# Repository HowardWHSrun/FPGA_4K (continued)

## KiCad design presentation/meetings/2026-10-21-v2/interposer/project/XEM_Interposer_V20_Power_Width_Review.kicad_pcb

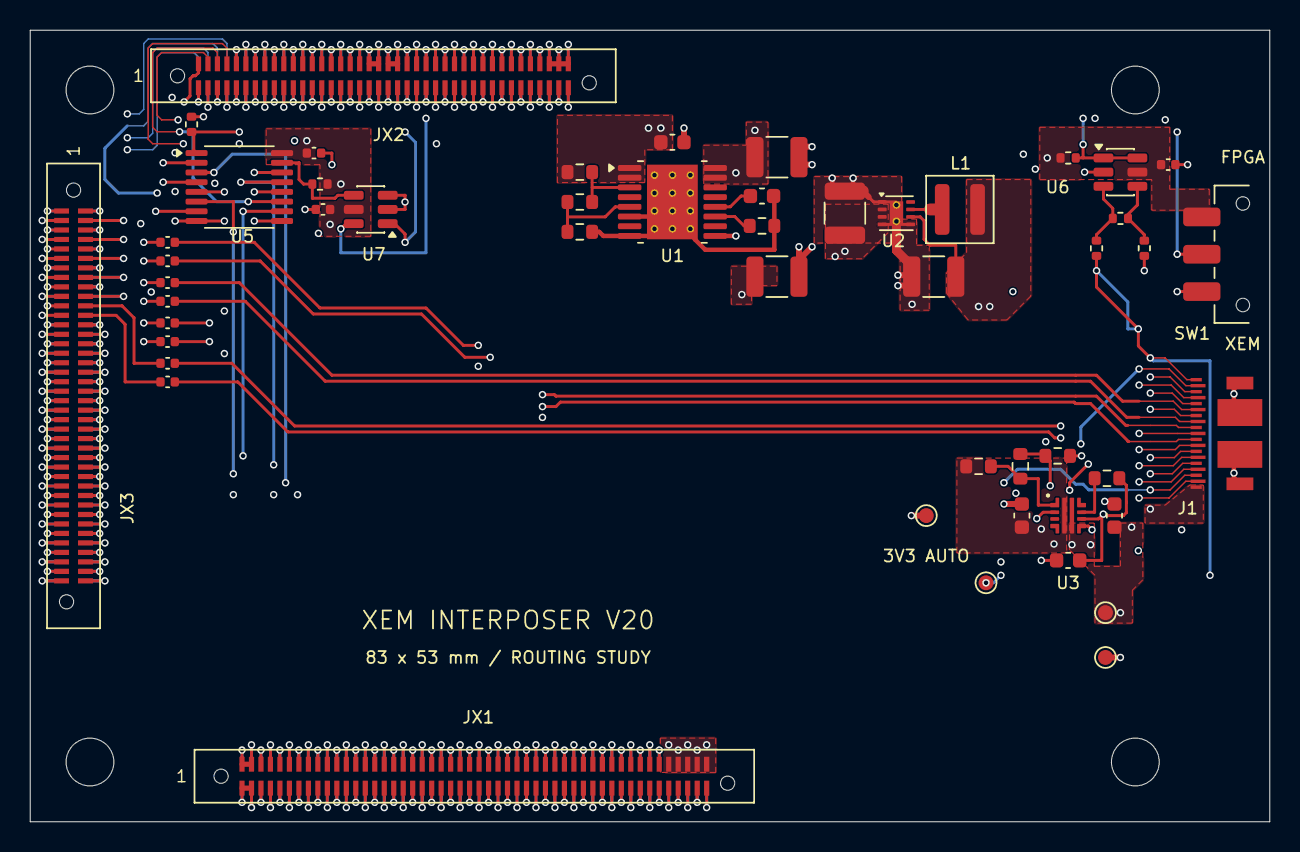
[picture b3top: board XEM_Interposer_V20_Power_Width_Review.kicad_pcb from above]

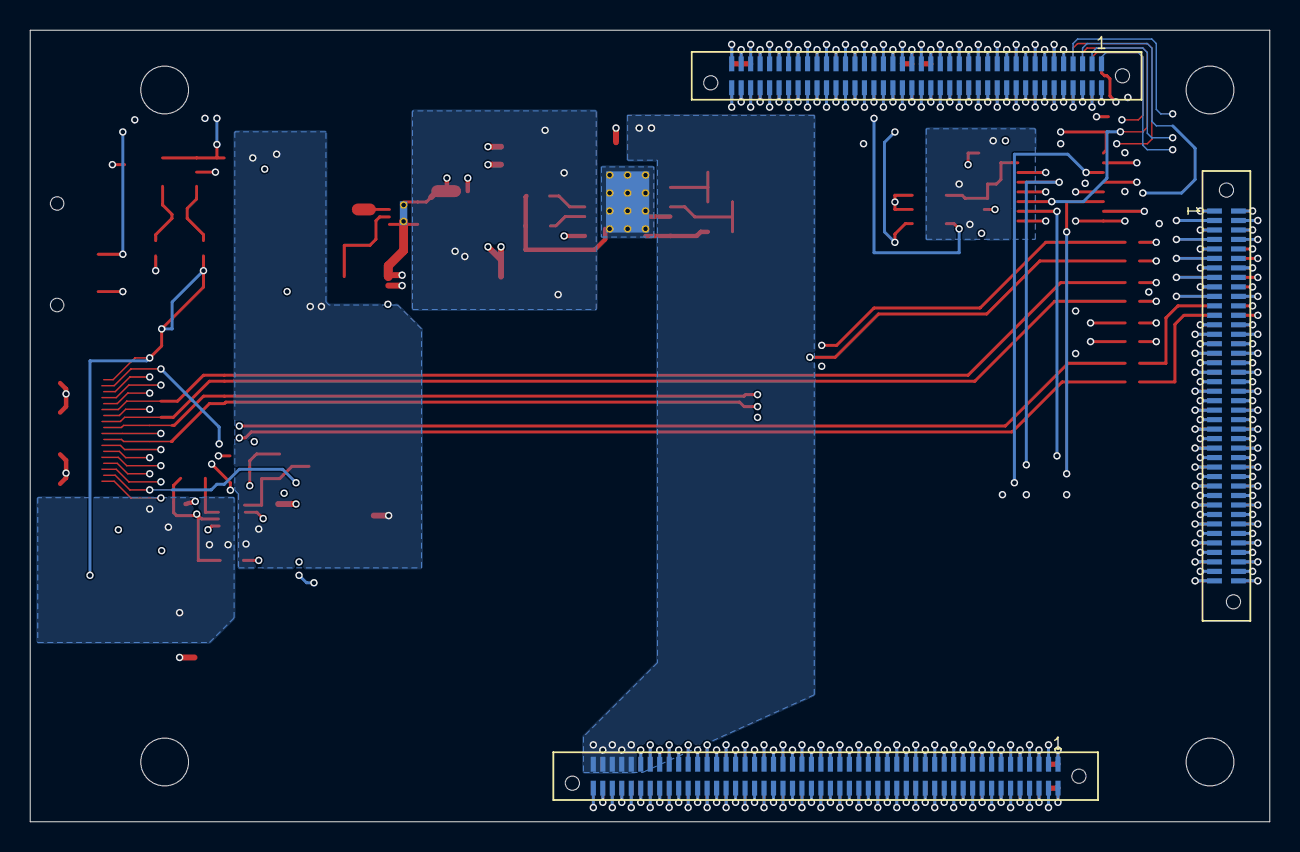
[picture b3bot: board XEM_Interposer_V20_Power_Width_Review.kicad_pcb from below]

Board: 6 copper layers, 83.0 x 53.0 mm, 57 parts (3 on the bottom side), 234 nets.

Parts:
C1: 1 µF / 50 V; C_0603_1608Metric
C2: 22 nF / 50 V; C_0603_1608Metric
C3, C10, C11: 10 uF / 50 V; C_1210_3225Metric
C4: 22 µF / 25 V; C_1210_3225Metric
C5, C7: 1 µF / 10 V; C_0603_1608Metric
C6: 3.3 nF / 10 V; C_0603_1608Metric
C12, C13, C14, C15, C16, C17, C18, C19: 100 nF / 16 V; C_0402_1005Metric
C20, C21, C22: 100 nF / 10 V; C_0402_1005Metric
J1: PKS019-4011-0; PKS019-4011-0_A114106_001_RevA_V17
JB1: ERM6-50-01.5-L-DV-A-K-TR; ERM6-50-01.5-L-DV-A-K-TR_SharedHoles_V16
JB2, JB3: ERM6-40-01.5-L-DV-A-K-TR; ERM6-40-01.5-L-DV-A-K-TR_SharedHoles_V16
JX1: ERF6-50-03.5-L-DV-A-K-TR
JX2, JX3: ERF6-40-03.5-L-DV-A-K-TR
L1: 2.2 µH; L_Coilcraft_XAL4020-XXX
MH1, MH2, MH3, MH4: 3.2 mm mounting datum
R1: 1.05 MΩ; R_0603_1608Metric
R2: 78.7 kΩ; R_0603_1608Metric
R3, R7: 100 kΩ; R_0603_1608Metric
R4: 12.1 kΩ; R_0603_1608Metric
R5: 174 kΩ; R_0603_1608Metric
R6: 24.9 kΩ; R_0603_1608Metric
R8: 6.49 kΩ; R_0603_1608Metric
R11: 75.0 k / 0.1%; R_0402_1005Metric
R12: 3.83 k / 0.1%; R_0402_1005Metric
R13: 20.0 k / 0.1%; R_0402_1005Metric
R14: 10 k; R_0402_1005Metric
R15: 47.0 k / 1%; R_0402_1005Metric
R16: 100 k; R_0402_1005Metric
SW1: JS102011SABN; SW_SPDT_CK_JS102011SABN
TP1: 3V3 LOCAL; TestPoint_Pad_D1.0mm
TP2: 3V3 CABLE; TestPoint_Pad_D1.0mm
TP3: TARGET 1V8 SENSE; TestPoint_Pad_D1.0mm
TP4: GND; TestPoint_Pad_D1.0mm
U1: TPS26600PWPR; HTSSOP-16-1EP_4.4x5mm_P0.65mm_EP3.4x5mm_Mask2.66x2.46mm_The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
U2: TPS62162DSGR; Texas_DSG0008A_WSON-8-1EP_2x2mm_P0.5mm_EP0.9x1.6mm_ThermalV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
U3: TPS259470ARPWR; TI_RPW0010A_HotRod_2x2mm
U5: TMUX1574PWR; TSSOP-16_4.4x5mm_P0.65mm
U6: TLV6700DDCR; SOT-23-6
U7: SN74LVC1G97DBVR; SOT-23-6

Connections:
+3V3_CABLE: C7.1, J1.19 (3V3_OUT), TP2.1 (1_1), U3.6 (OUT)
+3V3_LOCAL: C4.1, C5.1, C20.1, C21.1, C22.1, L1.2, R5.1, R14.1, R16.1, SW1.3, TP1.1 (1_1), U2.6 (VOS), U3.5 (IN), U5.16 (VDD), U6.5 (VDD), U7.5 (VCC)
/JTAG_DISABLE: R16.2, U5.15 (~EN), U7.4 (Y)
/JTAG_REMOTE_SELECT: R15.1, SW1.2 (C), U5.1 (SEL), U7.1 (IN1)
/TARGET_1V8_SENSE: J1.1 (TARGET_SENSE), R11.1, TP3.1 (1_1)
/TARGET_GOOD: R14.2, U6.1 (OUTA), U6.6 (OUTB), U7.6 (IN2)
/TARGET_OV_TAP: R12.2, R13.1, U6.4 (INB-)
/TARGET_TCK: J1.17 (TCK_1V8), U5.3 (S1B)
/TARGET_TDI: J1.15 (TDI_1V8), U5.6 (S2B)
/TARGET_TDO: J1.18 (TDO_1V8), U5.13 (S4B)
/TARGET_TMS: J1.2 (TMS_1V8), U5.10 (S3B)
/TARGET_UV_TAP: R11.2, R12.1, U6.3 (INA+)
BRK_REFCLK226_N: JB2.4 (REFCLK0N_226), JX2.4 (REFCLK0N_226)
BRK_REFCLK226_P: JB2.2 (REFCLK0P_226), JX2.2 (REFCLK0P_226)
BRK_TCK: JB2.1 (JTAG_TCK), U5.4 (D1)
BRK_TDI: JB2.3 (JTAG_TDI), U5.7 (D2)
BRK_TDO: JB2.7 (JTAG_TDO), U5.12 (D4)
BRK_TMS: JB2.5 (JTAG_TMS), U5.9 (D3)
BRK_VDCIN: C1.1, JB1.91 (VDCIN), JB1.93 (VDCIN), JB1.95 (VDCIN), JB1.97 (VDCIN), JB1.99 (VDCIN), JX1.91 (VDCIN), JX1.93 (VDCIN), JX1.95 (VDCIN), JX1.97 (VDCIN), JX1.99 (VDCIN), R1.1, U1.1 (IN), U1.2 (IN)
FPGA_RX1_N: C19.1, J1.14 (FPGA_RX1_N)
FPGA_RX1_P: C18.1, J1.12 (FPGA_RX1_P)
FPGA_TX0_N: C13.1, J1.5 (FPGA_TX0_N)
FPGA_TX0_P: C12.1, J1.3 (FPGA_TX0_P)
FPGA_TX1_N: C15.1, J1.8 (FPGA_TX1_N)
FPGA_TX1_P: C14.1, J1.6 (FPGA_TX1_P)
FPGA_TX2_N: C17.1, J1.11 (FPGA_TX2_N)
FPGA_TX2_P: C16.1, J1.9 (FPGA_TX2_P)
GND: C1.2, C3.2, C4.2, C5.2, C6.2, C7.2, C10.2, C11.2, C20.2, C21.2, C22.2, J1.4 (GND), J1.7 (GND), J1.10 (GND), J1.13 (GND), J1.16 (GND), J1.SH (SHELL), JB1.5 (GND), JB1.6 (GND), JB1.7 (GND), JB1.8 (GND), JB1.33 (GND), JB1.34 (GND), JB1.61 (GND), JB1.62 (GND), JB1.92 (GND), JB1.94 (GND), JB1.96 (GND), JB1.98 (GND), JB1.100 (GND), JB2.6 (GND), JB2.9 (GND), JB2.20 (GND), JB2.35 (GND), JB2.45 (GND), JB2.46 (GND), JB2.47 (GND), JB2.72 (GND), JB2.73 (GND), JB2.74 (GND), JB2.76 (GND), JB3.1 (GND), JB3.2 (GND), JB3.7 (GND), JB3.8 (GND), JB3.13 (GND), JB3.14 (GND), JB3.19 (GND), JB3.20 (GND), JB3.25 (GND), JB3.26 (GND), JB3.31 (GND), JB3.32 (GND), JB3.37 (GND), JB3.38 (GND), JB3.43 (GND), JB3.44 (GND), JB3.49 (GND), JB3.50 (GND), JB3.55 (GND), JB3.56 (GND), JB3.61 (GND), JB3.62 (GND), JB3.67 (GND), JB3.68 (GND), JB3.73 (GND), JB3.74 (GND), JB3.79 (GND), JB3.80 (GND), JX1.5 (GND), JX1.6 (GND), JX1.7 (GND), JX1.8 (GND), JX1.33 (GND), JX1.34 (GND), JX1.61 (GND), JX1.62 (GND), JX1.92 (GND), JX1.94 (GND), JX1.96 (GND), JX1.98 (GND), JX1.100 (GND), JX2.6 (GND), JX2.9 (GND), JX2.20 (GND), JX2.35 (GND), JX2.45 (GND), JX2.46 (GND), JX2.47 (GND), JX2.72 (GND), JX2.73 (GND), JX2.74 (GND), JX2.76 (GND), JX3.1 (GND), JX3.2 (GND), JX3.7 (GND), JX3.8 (GND), JX3.13 (GND), JX3.14 (GND), JX3.19 (GND), JX3.20 (GND), JX3.25 (GND), JX3.26 (GND), JX3.31 (GND), JX3.32 (GND), JX3.37 (GND), JX3.38 (GND), JX3.43 (GND), JX3.44 (GND), JX3.49 (GND), JX3.50 (GND), JX3.55 (GND), JX3.56 (GND), JX3.61 (GND), JX3.62 (GND), JX3.67 (GND), JX3.68 (GND), JX3.73 (GND), JX3.74 (GND), JX3.79 (GND), JX3.80 (GND), R7.2, R8.2, R13.2, R15.2, SW1.1, TP4.1 (1_1), U1.9 (GND), U2.1 (PGND), U2.4 (AGND), U2.5 (FB), U2.9 (EP), U3.8 (GND), U5.8 (GND), U6.2 (GND), U7.2 (GND), U7.3 (IN0)
INPUT_RTN: C2.2, R3.2, R4.2, U1.6 (MODE), U1.8 (RTN), U1.17 (RTN)
unnamed: C13.2, JX3.24 (MGT_RXN0_226)
unnamed: C15.2, JX3.18 (MGT_RXN1_226)
unnamed: C17.2, JX3.12 (MGT_RXN2_226)
unnamed: C12.2, JX3.22 (MGT_RXP0_226)
unnamed: C14.2, JX3.16 (MGT_RXP1_226)
unnamed: C16.2, JX3.10 (MGT_RXP2_226)
unnamed: C19.2, JX3.23 (MGT_TXN0_226)
unnamed: C18.2, JX3.21 (MGT_TXP0_226)
unnamed: R4.1, U1.11 (ILIM)
unnamed: R2.2, R3.1, U1.5 (OVP)
unnamed: R1.2, R2.1, U1.3 (UVLO)
unnamed: C2.1, U1.12 (dVdT)
unnamed: L1.1, U2.7 (SW)
unnamed: R5.2, R6.1, U3.1 (EN/UVLO)
unnamed: R8.1, U3.9 (ILM)
unnamed: R6.2, R7.1, U3.2 (OVLO)
unnamed: C6.1, U3.7 (dVdt)
PROTECTED_12V: C3.1, C10.1, C11.1, U1.15 (OUT), U1.16 (OUT), U2.2 (VIN), U2.3 (EN)
STACK_MC1_09: JB1.9 (B84_L7P_HDGC), JX1.9 (B84_L7P_HDGC)
STACK_MC1_10: JB1.10 (B84_L1P), JX1.10 (B84_L1P)
STACK_MC1_11: JB1.11 (B84_L7N_HDGC), JX1.11 (B84_L7N_HDGC)
STACK_MC1_12: JB1.12 (B84_L1N), JX1.12 (B84_L1N)
STACK_MC1_13: JB1.13 (B84_L8P_HDGC), JX1.13 (B84_L8P_HDGC)
STACK_MC1_14: JB1.14 (B84_L2P), JX1.14 (B84_L2P)
STACK_MC1_15: JB1.15 (B84_L8N_HDGC), JX1.15 (B84_L8N_HDGC)
STACK_MC1_16: JB1.16 (B84_L2N), JX1.16 (B84_L2N)
STACK_MC1_17: JB1.17 (B84_L9P), JX1.17 (B84_L9P)
STACK_MC1_18: JB1.18 (B84_L3P), JX1.18 (B84_L3P)
STACK_MC1_19: JB1.19 (B84_L9N), JX1.19 (B84_L9N)
STACK_MC1_20: JB1.20 (B84_L3N), JX1.20 (B84_L3N)
STACK_MC1_21: JB1.21 (B84_L10P), JX1.21 (B84_L10P)
STACK_MC1_22: JB1.22 (B84_L4P), JX1.22 (B84_L4P)
STACK_MC1_23: JB1.23 (B84_L10N), JX1.23 (B84_L10N)
STACK_MC1_24: JB1.24 (B84_L4N), JX1.24 (B84_L4N)
STACK_MC1_25: JB1.25 (B84_L11P), JX1.25 (B84_L11P)
STACK_MC1_26: JB1.26 (B84_L5P_HDGC), JX1.26 (B84_L5P_HDGC)
STACK_MC1_27: JB1.27 (B84_L11N), JX1.27 (B84_L11N)
STACK_MC1_28: JB1.28 (B84_L5N_HDGC), JX1.28 (B84_L5N_HDGC)
STACK_MC1_29: JB1.29 (B84_L12P), JX1.29 (B84_L12P)
STACK_MC1_30: JB1.30 (B84_L6P_HDGC), JX1.30 (B84_L6P_HDGC)
STACK_MC1_31: JB1.31 (B84_L12N), JX1.31 (B84_L12N)
STACK_MC1_32: JB1.32 (B84_L6N_HDGC), JX1.32 (B84_L6N_HDGC)
STACK_MC1_35: JB1.35 (B64_L24P), JX1.35 (B64_L24P)
STACK_MC1_36: JB1.36 (B64_L18P), JX1.36 (B64_L18P)
STACK_MC1_37: JB1.37 (B64_L24N), JX1.37 (B64_L24N)
STACK_MC1_38: JB1.38 (B64_L18N), JX1.38 (B64_L18N)
STACK_MC1_39: JB1.39 (B64_L23P), JX1.39 (B64_L23P)
STACK_MC1_40: JB1.40 (B64_L17P), JX1.40 (B64_L17P)
STACK_MC1_41: JB1.41 (B64_L23N), JX1.41 (B64_L23N)
STACK_MC1_42: JB1.42 (B64_L17N), JX1.42 (B64_L17N)
STACK_MC1_43: JB1.43 (B64_L22P), JX1.43 (B64_L22P)
STACK_MC1_44: JB1.44 (B64_L16P), JX1.44 (B64_L16P)
STACK_MC1_45: JB1.45 (B64_L22N), JX1.45 (B64_L22N)
STACK_MC1_46: JB1.46 (B64_L16N), JX1.46 (B64_L16N)
STACK_MC1_47: JB1.47 (B64_L21P), JX1.47 (B64_L21P)
STACK_MC1_48: JB1.48 (B64_L15P), JX1.48 (B64_L15P)
STACK_MC1_49: JB1.49 (B64_L21N), JX1.49 (B64_L21N)
STACK_MC1_50: JB1.50 (B64_L15N), JX1.50 (B64_L15N)
STACK_MC1_51: JB1.51 (B64_L20P), JX1.51 (B64_L20P)
STACK_MC1_52: JB1.52 (B64_L14P_GC), JX1.52 (B64_L14P_GC)
STACK_MC1_53: JB1.53 (B64_L20N), JX1.53 (B64_L20N)
STACK_MC1_54: JB1.54 (B64_L14N_GC), JX1.54 (B64_L14N_GC)
STACK_MC1_55: JB1.55 (B64_L19P), JX1.55 (B64_L19P)
STACK_MC1_56: JB1.56 (B64_L13P_GC), JX1.56 (B64_L13P_GC)
STACK_MC1_57: JB1.57 (B64_L19N), JX1.57 (B64_L19N)
STACK_MC1_58: JB1.58 (B64_L13N_GC), JX1.58 (B64_L13N_GC)
STACK_MC1_59: JB1.59 (B64_T3U_N12), JX1.59 (B64_T3U_N12)
STACK_MC1_60: JB1.60 (B64_T2U_N12), JX1.60 (B64_T2U_N12)
STACK_MC1_63: JB1.63 (B64_L12P_GC), JX1.63 (B64_L12P_GC)
STACK_MC1_64: JB1.64 (B64_L6P), JX1.64 (B64_L6P)
STACK_MC1_65: JB1.65 (B64_L12N_GC), JX1.65 (B64_L12N_GC)
STACK_MC1_66: JB1.66 (B64_L6N), JX1.66 (B64_L6N)
STACK_MC1_67: JB1.67 (B64_L11P_GC), JX1.67 (B64_L11P_GC)
STACK_MC1_68: JB1.68 (B64_L5P), JX1.68 (B64_L5P)
STACK_MC1_69: JB1.69 (B64_L11N_GC), JX1.69 (B64_L11N_GC)
STACK_MC1_70: JB1.70 (B64_L5N), JX1.70 (B64_L5N)
STACK_MC1_71: JB1.71 (B64_L10P), JX1.71 (B64_L10P)
STACK_MC1_72: JB1.72 (B64_L4P), JX1.72 (B64_L4P)
STACK_MC1_73: JB1.73 (B64_L10N), JX1.73 (B64_L10N)
STACK_MC1_74: JB1.74 (B64_L4N), JX1.74 (B64_L4N)
STACK_MC1_75: JB1.75 (B64_L9P), JX1.75 (B64_L9P)
STACK_MC1_76: JB1.76 (B64_L3P), JX1.76 (B64_L3P)
STACK_MC1_77: JB1.77 (B64_L9N), JX1.77 (B64_L9N)
STACK_MC1_78: JB1.78 (B64_L3N), JX1.78 (B64_L3N)
STACK_MC1_79: JB1.79 (B64_L8P), JX1.79 (B64_L8P)
STACK_MC1_80: JB1.80 (B64_L2P), JX1.80 (B64_L2P)
STACK_MC1_81: JB1.81 (B64_L8N), JX1.81 (B64_L8N)
STACK_MC1_82: JB1.82 (B64_L2N), JX1.82 (B64_L2N)
STACK_MC1_83: JB1.83 (B64_L7P), JX1.83 (B64_L7P)
STACK_MC1_84: JB1.84 (B64_L1P), JX1.84 (B64_L1P)
STACK_MC1_85: JB1.85 (B64_L7N), JX1.85 (B64_L7N)
STACK_MC1_86: JB1.86 (B64_L1N), JX1.86 (B64_L1N)
STACK_MC1_87: JB1.87 (RESERVED1), JX1.87 (RESERVED1)
STACK_MC1_88: JB1.88 (B64_T1U_N12), JX1.88 (B64_T1U_N12)
STACK_MC1_89: JB1.89 (VREF_64), JX1.89 (VREF_64)
STACK_MC1_90: JB1.90 (XEM8305_PG), JX1.90 (XEM8305_PG)
STACK_MC2_08: JB2.8 (VBATT), JX2.8 (VBATT)
STACK_MC2_10: JB2.10 (XADC_VN), JX2.10 (XADC_VN)
STACK_MC2_11: JB2.11 (B85_L1P), JX2.11 (B85_L1P)
STACK_MC2_12: JB2.12 (XADC_VP), JX2.12 (XADC_VP)
STACK_MC2_13: JB2.13 (B85_L1N), JX2.13 (B85_L1N)
STACK_MC2_14: JB2.14 (VREFP), JX2.14 (VREFP)
STACK_MC2_15: JB2.15 (B85_L2P), JX2.15 (B85_L2P)
STACK_MC2_16: JB2.16 (GNDADC), JX2.16 (GNDADC)
STACK_MC2_17: JB2.17 (B85_L2N), JX2.17 (B85_L2N)
STACK_MC2_18: JB2.18 (VCCADC), JX2.18 (VCCADC)
STACK_MC2_19: JB2.19 (B85_L3P), JX2.19 (B85_L3P)
STACK_MC2_21: JB2.21 (B85_L3N), JX2.21 (B85_L3N)
STACK_MC2_22: JB2.22 (B85_L7P_HDGC), JX2.22 (B85_L7P_HDGC)
STACK_MC2_23: JB2.23 (B85_L4P), JX2.23 (B85_L4P)
STACK_MC2_24: JB2.24 (B85_L7N_HDGC), JX2.24 (B85_L7N_HDGC)
STACK_MC2_25: JB2.25 (B85_L4N), JX2.25 (B85_L4N)
STACK_MC2_26: JB2.26 (B85_L8P_HDGC), JX2.26 (B85_L8P_HDGC)
STACK_MC2_27: JB2.27 (B85_L5P_HDGC), JX2.27 (B85_L5P_HDGC)
STACK_MC2_28: JB2.28 (B85_L8N_HDGC), JX2.28 (B85_L8N_HDGC)
STACK_MC2_29: JB2.29 (B85_L5N_HDGC), JX2.29 (B85_L5N_HDGC)
STACK_MC2_30: JB2.30 (B85_L9P), JX2.30 (B85_L9P)
STACK_MC2_31: JB2.31 (B85_L6P_HDGC), JX2.31 (B85_L6P_HDGC)
STACK_MC2_32: JB2.32 (B85_L9N), JX2.32 (B85_L9N)
STACK_MC2_33: JB2.33 (B85_L6N_HDGC), JX2.33 (B85_L6N_HDGC)
STACK_MC2_34: JB2.34 (B85_L10P), JX2.34 (B85_L10P)
STACK_MC2_36: JB2.36 (B85_L10N), JX2.36 (B85_L10N)
STACK_MC2_38: JB2.38 (B85_L11P), JX2.38 (B85_L11P)
STACK_MC2_40: JB2.40 (B85_L11N), JX2.40 (B85_L11N)
STACK_MC2_42: JB2.42 (B85_L12P), JX2.42 (B85_L12P)
STACK_MC2_44: JB2.44 (B85_L12N), JX2.44 (B85_L12N)
STACK_MC2_48: JB2.48 (B86_L12P), JX2.48 (B86_L12P)
STACK_MC2_49: JB2.49 (B86_L6P_HDGC), JX2.49 (B86_L6P_HDGC)
STACK_MC2_50: JB2.50 (B86_L12N), JX2.50 (B86_L12N)
STACK_MC2_51: JB2.51 (B86_L6N_HDGC), JX2.51 (B86_L6N_HDGC)
STACK_MC2_52: JB2.52 (B86_L11P), JX2.52 (B86_L11P)
STACK_MC2_53: JB2.53 (B86_L5P_HDGC), JX2.53 (B86_L5P_HDGC)
STACK_MC2_54: JB2.54 (B86_L11N), JX2.54 (B86_L11N)
STACK_MC2_55: JB2.55 (B86_L5N_HDGC), JX2.55 (B86_L5N_HDGC)
STACK_MC2_56: JB2.56 (B86_L10P), JX2.56 (B86_L10P)
STACK_MC2_57: JB2.57 (B86_L4P), JX2.57 (B86_L4P)
STACK_MC2_58: JB2.58 (B86_L10N), JX2.58 (B86_L10N)
STACK_MC2_59: JB2.59 (B86_L4N), JX2.59 (B86_L4N)
STACK_MC2_60: JB2.60 (B86_L9P), JX2.60 (B86_L9P)
STACK_MC2_61: JB2.61 (B86_L3P), JX2.61 (B86_L3P)
STACK_MC2_62: JB2.62 (B86_L9N), JX2.62 (B86_L9N)
STACK_MC2_63: JB2.63 (B86_L3N), JX2.63 (B86_L3N)
STACK_MC2_64: JB2.64 (B86_L8P_HDGC), JX2.64 (B86_L8P_HDGC)
STACK_MC2_65: JB2.65 (B86_L2P), JX2.65 (B86_L2P)
STACK_MC2_66: JB2.66 (B86_L8N_HDGC), JX2.66 (B86_L8N_HDGC)
STACK_MC2_67: JB2.67 (B86_L2N), JX2.67 (B86_L2N)
STACK_MC2_68: JB2.68 (B86_L7P_HDGC), JX2.68 (B86_L7P_HDGC)
STACK_MC2_69: JB2.69 (B86_L1P), JX2.69 (B86_L1P)
STACK_MC2_70: JB2.70 (B86_L7N_HDGC), JX2.70 (B86_L7N_HDGC)
STACK_MC2_71: JB2.71 (B86_L1N), JX2.71 (B86_L1N)
STACK_MC2_78: JB2.78 (DXP), JX2.78 (DXP)
STACK_MC2_80: JB2.80 (DXN), JX2.80 (DXN)
STACK_MC3_03: JB3.3 (MGT_TXP3_226), JX3.3 (MGT_TXP3_226)
STACK_MC3_04: JB3.4 (MGT_RXP3_226), JX3.4 (MGT_RXP3_226)
STACK_MC3_05: JB3.5 (MGT_TXN3_226), JX3.5 (MGT_TXN3_226)
STACK_MC3_06: JB3.6 (MGT_RXN3_226), JX3.6 (MGT_RXN3_226)
STACK_MC3_09: JB3.9 (MGT_TXP2_226), JX3.9 (MGT_TXP2_226)
STACK_MC3_11: JB3.11 (MGT_TXN2_226), JX3.11 (MGT_TXN2_226)
STACK_MC3_15: JB3.15 (MGT_TXP1_226), JX3.15 (MGT_TXP1_226)
STACK_MC3_17: JB3.17 (MGT_TXN1_226), JX3.17 (MGT_TXN1_226)
STACK_MC3_27: JB3.27 (MGT_TXP3_225), JX3.27 (MGT_TXP3_225)
STACK_MC3_28: JB3.28 (MGT_RXP3_225), JX3.28 (MGT_RXP3_225)
STACK_MC3_29: JB3.29 (MGT_TXN3_225), JX3.29 (MGT_TXN3_225)
STACK_MC3_30: JB3.30 (MGT_RXN3_225), JX3.30 (MGT_RXN3_225)
STACK_MC3_33: JB3.33 (MGT_TXP2_225), JX3.33 (MGT_TXP2_225)
STACK_MC3_34: JB3.34 (MGT_RXP2_225), JX3.34 (MGT_RXP2_225)
STACK_MC3_35: JB3.35 (MGT_TXN2_225), JX3.35 (MGT_TXN2_225)
STACK_MC3_36: JB3.36 (MGT_RXN2_225), JX3.36 (MGT_RXN2_225)
STACK_MC3_39: JB3.39 (MGT_TXP1_225), JX3.39 (MGT_TXP1_225)
STACK_MC3_40: JB3.40 (MGT_RXP1_225), JX3.40 (MGT_RXP1_225)
STACK_MC3_41: JB3.41 (MGT_TXN1_225), JX3.41 (MGT_TXN1_225)
STACK_MC3_42: JB3.42 (MGT_RXN1_225), JX3.42 (MGT_RXN1_225)
STACK_MC3_45: JB3.45 (MGT_TXP0_225), JX3.45 (MGT_TXP0_225)
STACK_MC3_46: JB3.46 (MGT_RXP0_225), JX3.46 (MGT_RXP0_225)
STACK_MC3_47: JB3.47 (MGT_TXN0_225), JX3.47 (MGT_TXN0_225)
STACK_MC3_48: JB3.48 (MGT_RXN0_225), JX3.48 (MGT_RXN0_225)
STACK_MC3_51: JB3.51 (REFCLK0P_224), JX3.51 (REFCLK0P_224)
STACK_MC3_52: JB3.52 (REFCLK0P_225), JX3.52 (REFCLK0P_225)
STACK_MC3_53: JB3.53 (REFCLK0N_224), JX3.53 (REFCLK0N_224)
STACK_MC3_54: JB3.54 (REFCLK0N_225), JX3.54 (REFCLK0N_225)
STACK_MC3_57: JB3.57 (MGT_TXP3_224), JX3.57 (MGT_TXP3_224)
STACK_MC3_58: JB3.58 (MGT_RXP3_224), JX3.58 (MGT_RXP3_224)
STACK_MC3_59: JB3.59 (MGT_TXN3_224), JX3.59 (MGT_TXN3_224)
STACK_MC3_60: JB3.60 (MGT_RXN3_224), JX3.60 (MGT_RXN3_224)
STACK_MC3_63: JB3.63 (MGT_TXP2_224), JX3.63 (MGT_TXP2_224)
STACK_MC3_64: JB3.64 (MGT_RXP2_224), JX3.64 (MGT_RXP2_224)
STACK_MC3_65: JB3.65 (MGT_TXN2_224), JX3.65 (MGT_TXN2_224)
STACK_MC3_66: JB3.66 (MGT_RXN2_224), JX3.66 (MGT_RXN2_224)
STACK_MC3_69: JB3.69 (MGT_TXP1_224), JX3.69 (MGT_TXP1_224)
STACK_MC3_70: JB3.70 (MGT_RXP1_224), JX3.70 (MGT_RXP1_224)
STACK_MC3_71: JB3.71 (MGT_TXN1_224), JX3.71 (MGT_TXN1_224)
STACK_MC3_72: JB3.72 (MGT_RXN1_224), JX3.72 (MGT_RXN1_224)
STACK_MC3_75: JB3.75 (MGT_TXP0_224), JX3.75 (MGT_TXP0_224)
STACK_MC3_76: JB3.76 (MGT_RXP0_224), JX3.76 (MGT_RXP0_224)
STACK_MC3_77: JB3.77 (MGT_TXN0_224), JX3.77 (MGT_TXN0_224)
STACK_MC3_78: JB3.78 (MGT_RXN0_224), JX3.78 (MGT_RXN0_224)
VCCO_64: JB1.2 (VCCO_64), JB1.4 (VCCO_64), JX1.2 (VCCO_64), JX1.4 (VCCO_64)
VCCO_84: JB1.1 (VCCO_84), JB1.3 (VCCO_84), JX1.1 (VCCO_84), JX1.3 (VCCO_84)
VCCO_85: JB2.37 (VCCO_85), JB2.39 (VCCO_85), JX2.37 (VCCO_85), JX2.39 (VCCO_85)
VCCO_86: JB2.41 (VCCO_86), JB2.43 (VCCO_86), JX2.41 (VCCO_86), JX2.43 (VCCO_86)
XEM_1V8_OUT: JB2.75 (1V8_OUT), JB2.77 (1V8_OUT), JB2.79 (1V8_OUT), JX2.75 (1V8_OUT), JX2.77 (1V8_OUT), JX2.79 (1V8_OUT)
XEM_TCK: JX2.1 (JTAG_TCK), U5.2 (S1A)
XEM_TDI: JX2.3 (JTAG_TDI), U5.5 (S2A)
XEM_TDO: JX2.7 (JTAG_TDO), U5.14 (S4A)
XEM_TMS: JX2.5 (JTAG_TMS), U5.11 (S3A)

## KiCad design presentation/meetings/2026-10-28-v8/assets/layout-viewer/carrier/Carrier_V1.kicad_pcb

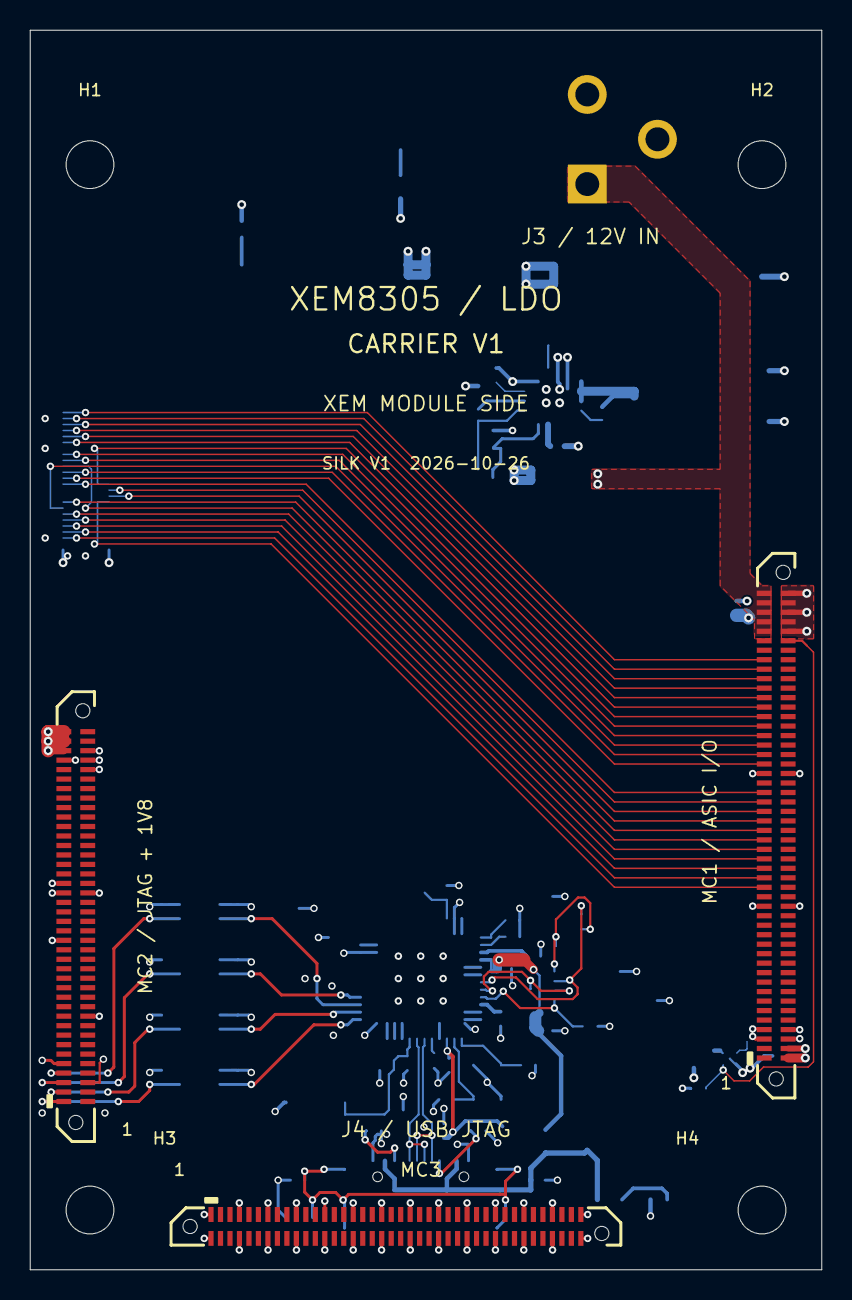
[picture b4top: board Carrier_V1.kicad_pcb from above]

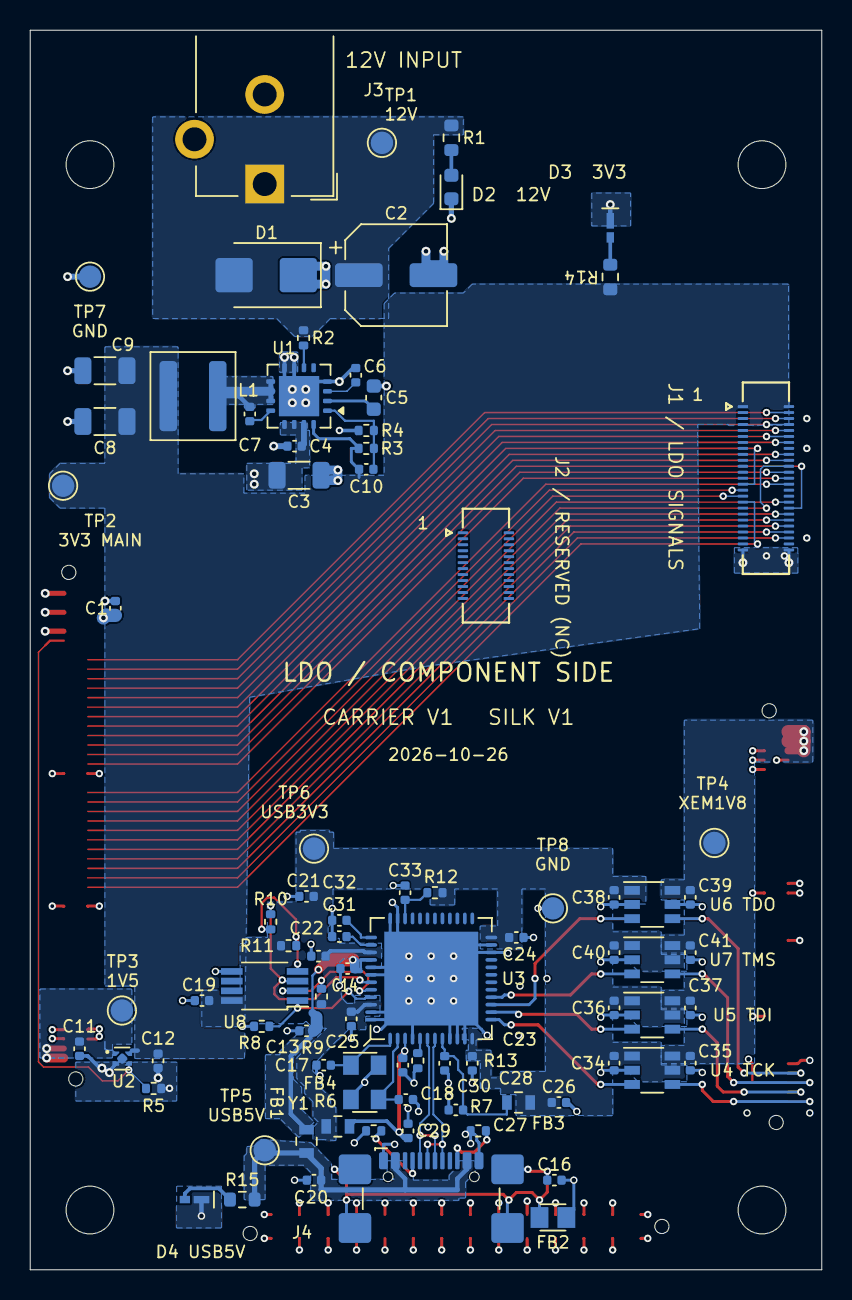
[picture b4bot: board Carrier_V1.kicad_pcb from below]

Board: 4 copper layers, 53.0 x 83.0 mm, 92 parts (85 on the bottom side), 66 nets.

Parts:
C1: 0.1u 25v; C_0402_1005Metric
C2: 220u 25v; CP_Panasonic_EEE-FTE221XAP_D6.3x7.7
C3: 22u 35V; C_1206_3216Metric
C4: 0.1u 25V; C_0402_1005Metric
C5: 1u 25V; C_0603_1608Metric
C6: 3.3n 50V; C_0402_1005Metric
C7: 0.1u 16V; C_0402_1005Metric
C8, C9: 22u 10V; C_1206_3216Metric
C10: 10p 50V; C_0402_1005Metric
C11, C12: 4.7u 10V X5R; C_0402_1005Metric
C13, C21, C26, C27, C29: 4.7u; C_0402_1005Metric
C14, C16, C19, C22, C23, C24, C25, C28, C30, C31, C32, C34, C35, C36, C37, C38, C39, C40, C41: 100n; C_0402_1005Metric
C17, C18: 18p; C_0402_1005Metric
C20, C33: 10n; C_0402_1005Metric
D1: SMBJ15CA-13-F; D_SMB
D2: 598-8070-107F; LED_0603_1608Metric
D3: AA1608LCGSK; LED_Kingbright_AA1608_1.6x0.8mm
D4: AA1608LSYSK; LED_Kingbright_AA1608_1.6x0.8mm
FB1, FB3, FB4: 600R; Ferrite_Bead_Laird_MI0603_1608Metric
FB2: 220R @100MHz; BRK8305_A03_FB503
H1, H2, H3, H4: XEM M3 NPTH; MountingHole_3.2mm_XEM_M3_Keepout
J1: LDO_50DS; Hirose_DF40C(2.0)-50DS-0.4V_2x25_P0.4mm
J2: LDO_24DS; Hirose_DF40C(2.0)-24DS-0.4V_2x12_P0.4mm
J3: PJ-102AH; PJ102AH
J4: USB4110-GF-A; USB_C_Receptacle_GCT_USB4110_GF_A_Horizontal
L1: 3.3uH; L_Coilcraft_XAL5030-332MEC
MC1: ERF6-50-03.5-L-DV-A-K-TR
MC2: XEM_MC2_80; ERF6-40-03.5-L-DV-A-K-TR
MC3: XEM_MC3_80; ERF6-40-03.5-L-DV-A-K-TR
R1: 2.0k; R_0603_1608Metric
R2: 10k 1%; R_0402_1005Metric
R3: 73.2k 1%; R_0402_1005Metric
R4: 22.1k 1%; R_0402_1005Metric
R5, R8, R9: 100k; R_0402_1005Metric
R6, R7: 5.1k 1%; R_0402_1005Metric
R10: 2k; R_0402_1005Metric
R11, R12: 10k; R_0402_1005Metric
R13: 12k 1%; R_0402_1005Metric
R14: 3.0k 1%; R_0603_1608Metric
R15: 6.8k 1%; R_0603_1608Metric
TP1: 12V; TestPoint_Pad_D1.5mm
TP2: 3V3_MAIN; TestPoint_Pad_D1.5mm
TP3: 1V5; TestPoint_Pad_D1.5mm
TP4: XEM_1V8; TestPoint_Pad_D1.5mm
TP5: USB_5V; TestPoint_Pad_D1.5mm
TP6: USB_3V3; TestPoint_Pad_D1.5mm
TP7: GND_PWR; TestPoint_Pad_D1.5mm
TP8: GND_USB; TestPoint_Pad_D1.5mm
U1: TPS54429ERSAR; TPS54429E_RSA
U2: TLV75515PDQNR; Texas_X2SON-4_1x1mm_P0.65mm
U3: FT232HQ; BRK8305_A03_U501
U4, U5, U6, U7: SN74AXC1T45DBVR; BRK8305_A03_U500
U8: 93LC56B-E/MS; BRK8305_A03_U505
Y1: 12MHz; BRK8305_A03_Y500

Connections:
+1V5: C11.1, MC1.2 (VCCO_64), MC1.4 (VCCO_64), TP3.1, U2.1
+3V3: C8.1, C9.1, C10.1, C12.1, J1.1 (3V3), J1.2 (3V3), L1.2, R3.1, R14.1, TP2.1, U1.16 (VO), U2.4
+12V: C1.1, C2.1, C3.1, C4.1, D1.2 (A2), J3.1, MC1.91 (VDCIN), MC1.93 (VDCIN), MC1.95 (VDCIN), MC1.97 (VDCIN), MC1.99 (VDCIN), R1.1, R2.1, TP1.1, U1.13 (VIN1), U1.14 (VIN2), U1.15 (VIN3)
/FB_BUCK: C10.2, R3.2, R4.1, U1.1 (VFB)
/USBJTAG_1.8V_ANALOG: C32.2, U3.37
/USBJTAG_1.8V_CORE: C31.2, U3.38
/USBJTAG_3.3V: C19.1, C21.1, C22.1, C23.1, C24.1, C25.1, C26.1, C34.1, C36.1, C38.1, C40.1, FB3.1, FB4.1, R9.1, R11.2, R12.1, TP6.1, U3.12, U3.24, U3.39, U3.46, U4.1, U4.5, U5.1, U5.5, U6.1, U7.1, U7.5, U8.8
/USBJTAG_3.3V_PHY: C29.1, C30.1, FB4.2, U3.3
/USBJTAG_3.3V_PLL: C27.1, C28.1, FB3.2, U3.8
/USBJTAG_5V_FILTERED: C13.1, C14.1, FB1.2, U3.40
/USBJTAG_EECLK: R9.2, U3.44, U8.2
/USBJTAG_EECS: R8.1, U3.45, U8.1
/USBJTAG_EEDATA: R10.1, U3.43, U8.3
/XEM_1.8V: C35.1, C37.1, C39.1, C41.1, MC2.75 (1V8_OUT), MC2.77 (1V8_OUT), MC2.79 (1V8_OUT), TP4.1, U4.6, U5.6, U6.6, U7.6
CHIP_RESET: J1.14 (CHIP_RESET), MC1.75 (B64_L9P)
CLK32MHZ: J1.36 (CLK32MHZ), MC1.67 (B64_L11P_GC)
CLKH: J1.12 (CLKH), MC1.77 (B64_L9N)
D1: J1.4 (D1), MC1.85 (B64_L7N)
D2: J1.6 (D2), MC1.83 (B64_L7P)
D3: J1.8 (D3), MC1.81 (B64_L8N)
D4: J1.10 (D4), MC1.79 (B64_L8P)
D5: J1.38 (D5), MC1.47 (B64_L21P)
D6: J1.40 (D6), MC1.45 (B64_L22N)
D7: J1.42 (D7), MC1.43 (B64_L22P)
D8: J1.44 (D8), MC1.41 (B64_L23N)
FE_RESET: J1.20 (FE_RESET), MC1.69 (B64_L11N_GC)
GND: C1.2, C2.2, C3.2, C4.2, C5.1, C6.1, C8.2, C9.2, C11.2, C12.2, C13.2, C14.2, C16.2, C17.2, C18.2, C19.2, C20.1, C21.2, C22.2, C23.2, C24.2, C25.2, C26.2, C27.2, C28.2, C29.2, C30.2, C31.1, C32.1, C33.2, C34.2, C35.2, C36.2, C37.2, C38.2, C39.2, C40.2, C41.2, D1.1 (A1), D2.1 (K), D3.1, D4.1, FB2.1, J1.49 (DGND), J1.50 (DGND), J3.2, J4.A1, J4.A12, J4.B1, J4.B12, MC1.5 (DGND), MC1.6 (DGND), MC1.7 (DGND), MC1.8 (DGND), MC1.33 (DGND), MC1.34 (DGND), MC1.61 (DGND), MC1.62 (DGND), MC1.92 (DGND), MC1.94 (DGND), MC1.96 (DGND), MC1.98 (DGND), MC1.100 (DGND), MC2.6 (DGND), MC2.9 (DGND), MC2.20 (DGND), MC2.35 (DGND), MC2.45 (DGND), MC2.46 (DGND), MC2.47 (DGND), MC2.72 (DGND), MC2.73 (DGND), MC2.74 (DGND), MC2.76 (DGND), MC3.1 (DGND), MC3.2 (DGND), MC3.7 (DGND), MC3.8 (DGND), MC3.13 (DGND), MC3.14 (DGND), MC3.19 (DGND), MC3.20 (DGND), MC3.25 (DGND), MC3.26 (DGND), MC3.31 (DGND), MC3.32 (DGND), MC3.37 (DGND), MC3.38 (DGND), MC3.43 (DGND), MC3.44 (DGND), MC3.49 (DGND), MC3.50 (DGND), MC3.55 (DGND), MC3.56 (DGND), MC3.61 (DGND), MC3.62 (DGND), MC3.67 (DGND), MC3.68 (DGND), MC3.73 (DGND), MC3.74 (DGND), MC3.79 (DGND), MC3.80 (DGND), R4.2, R5.2, R6.1, R7.2, R8.2, R13.2, TP7.1, TP8.1, U1.4 (GND), U1.7 (PGND1), U1.8 (PGND2), U1.17 (EP/PGND), U2.2, U2.5, U3.4, U3.9, U3.10, U3.11, U3.22, U3.23, U3.35, U3.36, U3.41, U3.42, U3.47, U3.48, U3.PAD, U4.2, U5.2, U6.2, U6.5, U7.2, U8.5, Y1.2, Y1.4
IMP_TEST: J1.18 (IMP_TEST), MC1.71 (B64_L10P)
JTAG_TCK_1.8V: MC2.1 (JTAG_TCK), U4.4
JTAG_TDI_1.8V: MC2.3 (JTAG_TDI), U5.4
JTAG_TDO_1.8V: MC2.7 (JTAG_TDO), U6.4
JTAG_TMS_1.8V: MC2.5 (JTAG_TMS), U7.4
unnamed: C16.1, FB2.2, J4.M1, J4.M2, J4.M3, J4.M4
unnamed: D2.2 (A), R1.2
unnamed: D3.2, R14.2
unnamed: D4.2, R15.2
unnamed: J4.A5, R6.2
unnamed: J4.B5, R7.1
unnamed: R2.2, U1.6 (EN)
unnamed: C6.2, U1.3 (SS)
unnamed: C7.2, L1.1, U1.9 (SW1), U1.10 (SW2), U1.11 (SW3)
unnamed: C7.1, U1.12 (VBST)
unnamed: C5.2, U1.2 (VREG5)
unnamed: U3.13, U4.3
unnamed: U3.14, U5.3
unnamed: U3.15, U6.3
unnamed: U3.16, U7.3
unnamed: C17.1, U3.1, Y1.1
unnamed: C18.1, U3.2, Y1.3
unnamed: R13.1, U3.5
unnamed: C33.1, R12.2, U3.34
unnamed: R10.2, R11.1, U8.4
READ: J1.46 (READ), MC1.39 (B64_L23P)
SPI_CLK: J1.22 (SPI_CLK), MC1.49 (B64_L21N)
SPI_DINL: J1.26 (SPI_DINL), MC1.63 (B64_L12P_GC)
SPI_DINR: J1.28 (SPI_DINR), MC1.57 (B64_L19N)
SPI_LATCH: J1.24 (SPI_LATCH), MC1.65 (B64_L12N_GC)
STIM_CHB: J1.33 (STIM_CHB), MC1.37 (B64_L24N)
STIM_CLK: J1.29 (STIM_CLK), MC1.55 (B64_L19P)
STIM_EN: J1.31 (STIM_EN), MC1.53 (B64_L20N)
STIM_START: J1.27 (STIM_START), MC1.73 (B64_L10N)
SYNC: J1.34 (SYNC), MC1.51 (B64_L20P)
USBJTAG_5V_IN: C20.2, FB1.1, J4.A4, J4.A9, J4.B4, J4.B9, R15.1, TP5.1
USB_D_N: J4.A7, J4.B7, U3.6
USB_D_P: J4.A6, J4.B6, U3.7
XEM PG: MC1.90 (XEM8305_PG), R5.1, U2.3
